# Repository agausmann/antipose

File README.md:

# antipose

A tiny MX switch breakout board.

## Features

- 5 keys, one for each finger and thumb
- Hot-swappable (Kailh sockets)
- Reversible/mirrored layout on both sides (e.g. make one for each hand)
- Simple pin header connections

## Motivation

I had a small sample pack of 10 keyboard switches, and I wanted to test how
they feel in osu!mania. I figured I could just attach them to a breadboard and
make a simple keyboard controller out of an Arduino or something, but the PCB
mount pins and the stem cutout got in the way of the breadboard, and they
simply would not fit. So I made this PCB to solve that!

I also realized this is pretty similar to the [ASETNIOP](https://asetniop.com)
layout, hence the name (which is an anagram of ASETNIOP). I imagine this PCB could also
be used to try out ASETNIOP if you want to.

At first I thought about adding a microcontroller and USB port, but I realized
it's really not worth the hassle (time, money, and design effort). It's much
easier to have a generic pin header that you can adapt to whatever you have
lying around.

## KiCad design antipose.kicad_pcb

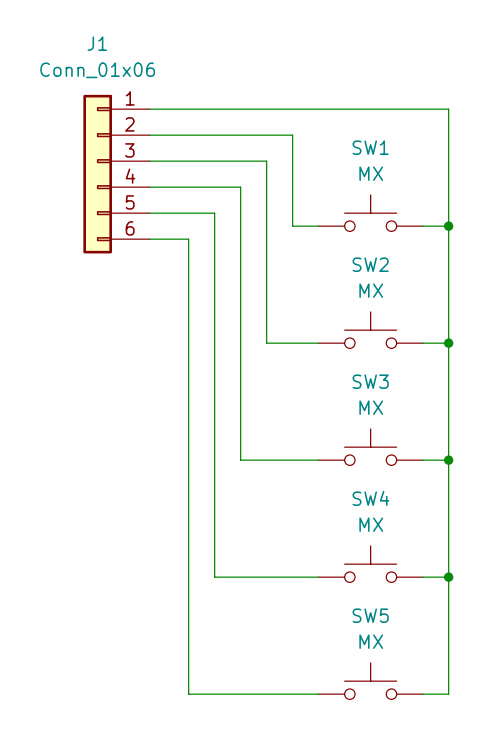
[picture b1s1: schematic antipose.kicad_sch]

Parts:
J1: Conn_01x06; PinHeader_1x06_P2.54mm_Vertical
SW1, SW2, SW3, SW4, SW5: MX; Kailh_HotSwap_Reversible_1u

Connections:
unnamed: J1.1, SW1.1, SW2.1, SW3.1, SW4.1, SW5.1
unnamed: J1.2, SW1.2
unnamed: J1.3, SW2.2
unnamed: J1.4, SW3.2
unnamed: J1.5, SW4.2
unnamed: J1.6, SW5.2

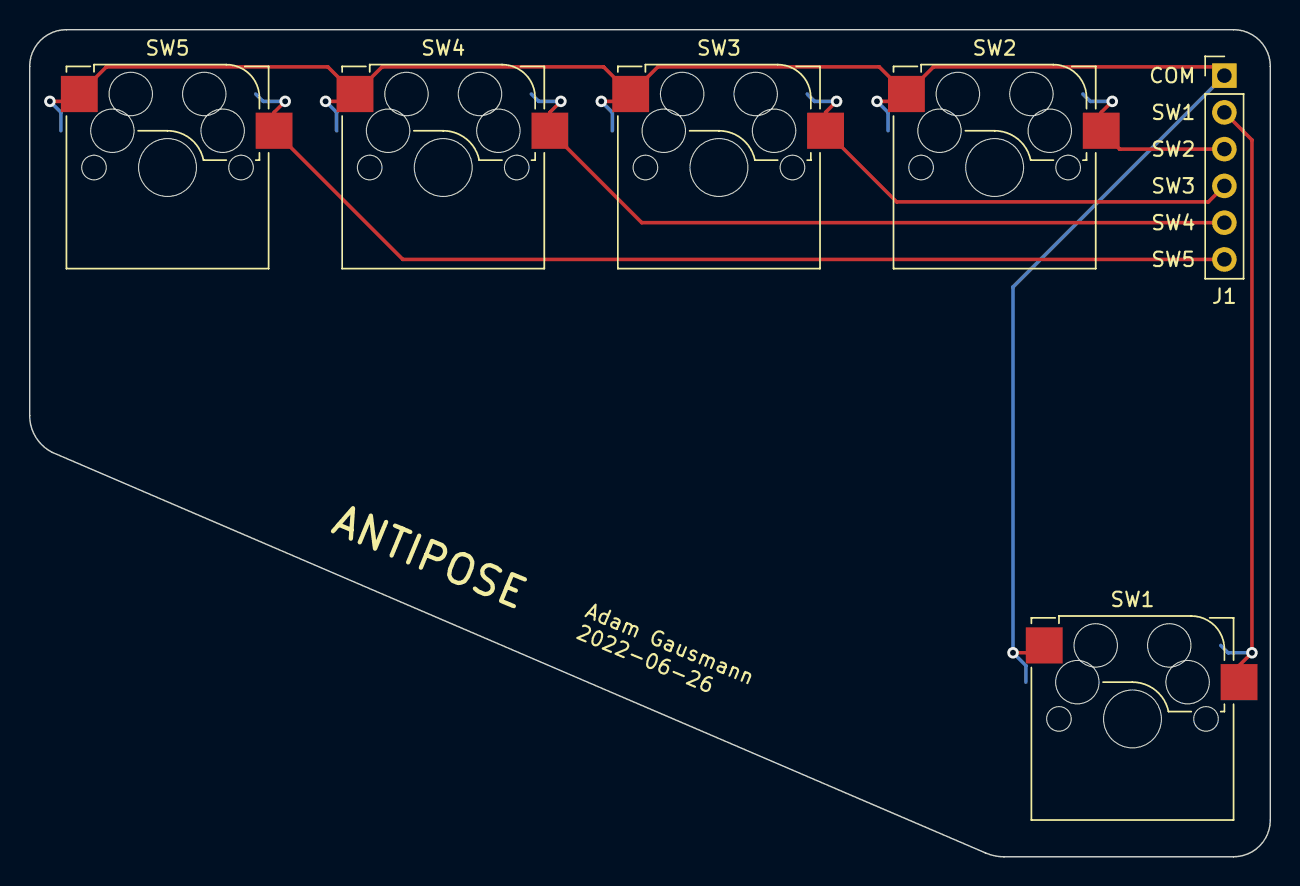
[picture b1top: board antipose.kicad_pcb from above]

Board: 2 copper layers, 85.7 x 57.1 mm, 6 parts (0 on the bottom side), 6 nets.

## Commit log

2022-06-26 Add antipose rev1 schematic & PCB
